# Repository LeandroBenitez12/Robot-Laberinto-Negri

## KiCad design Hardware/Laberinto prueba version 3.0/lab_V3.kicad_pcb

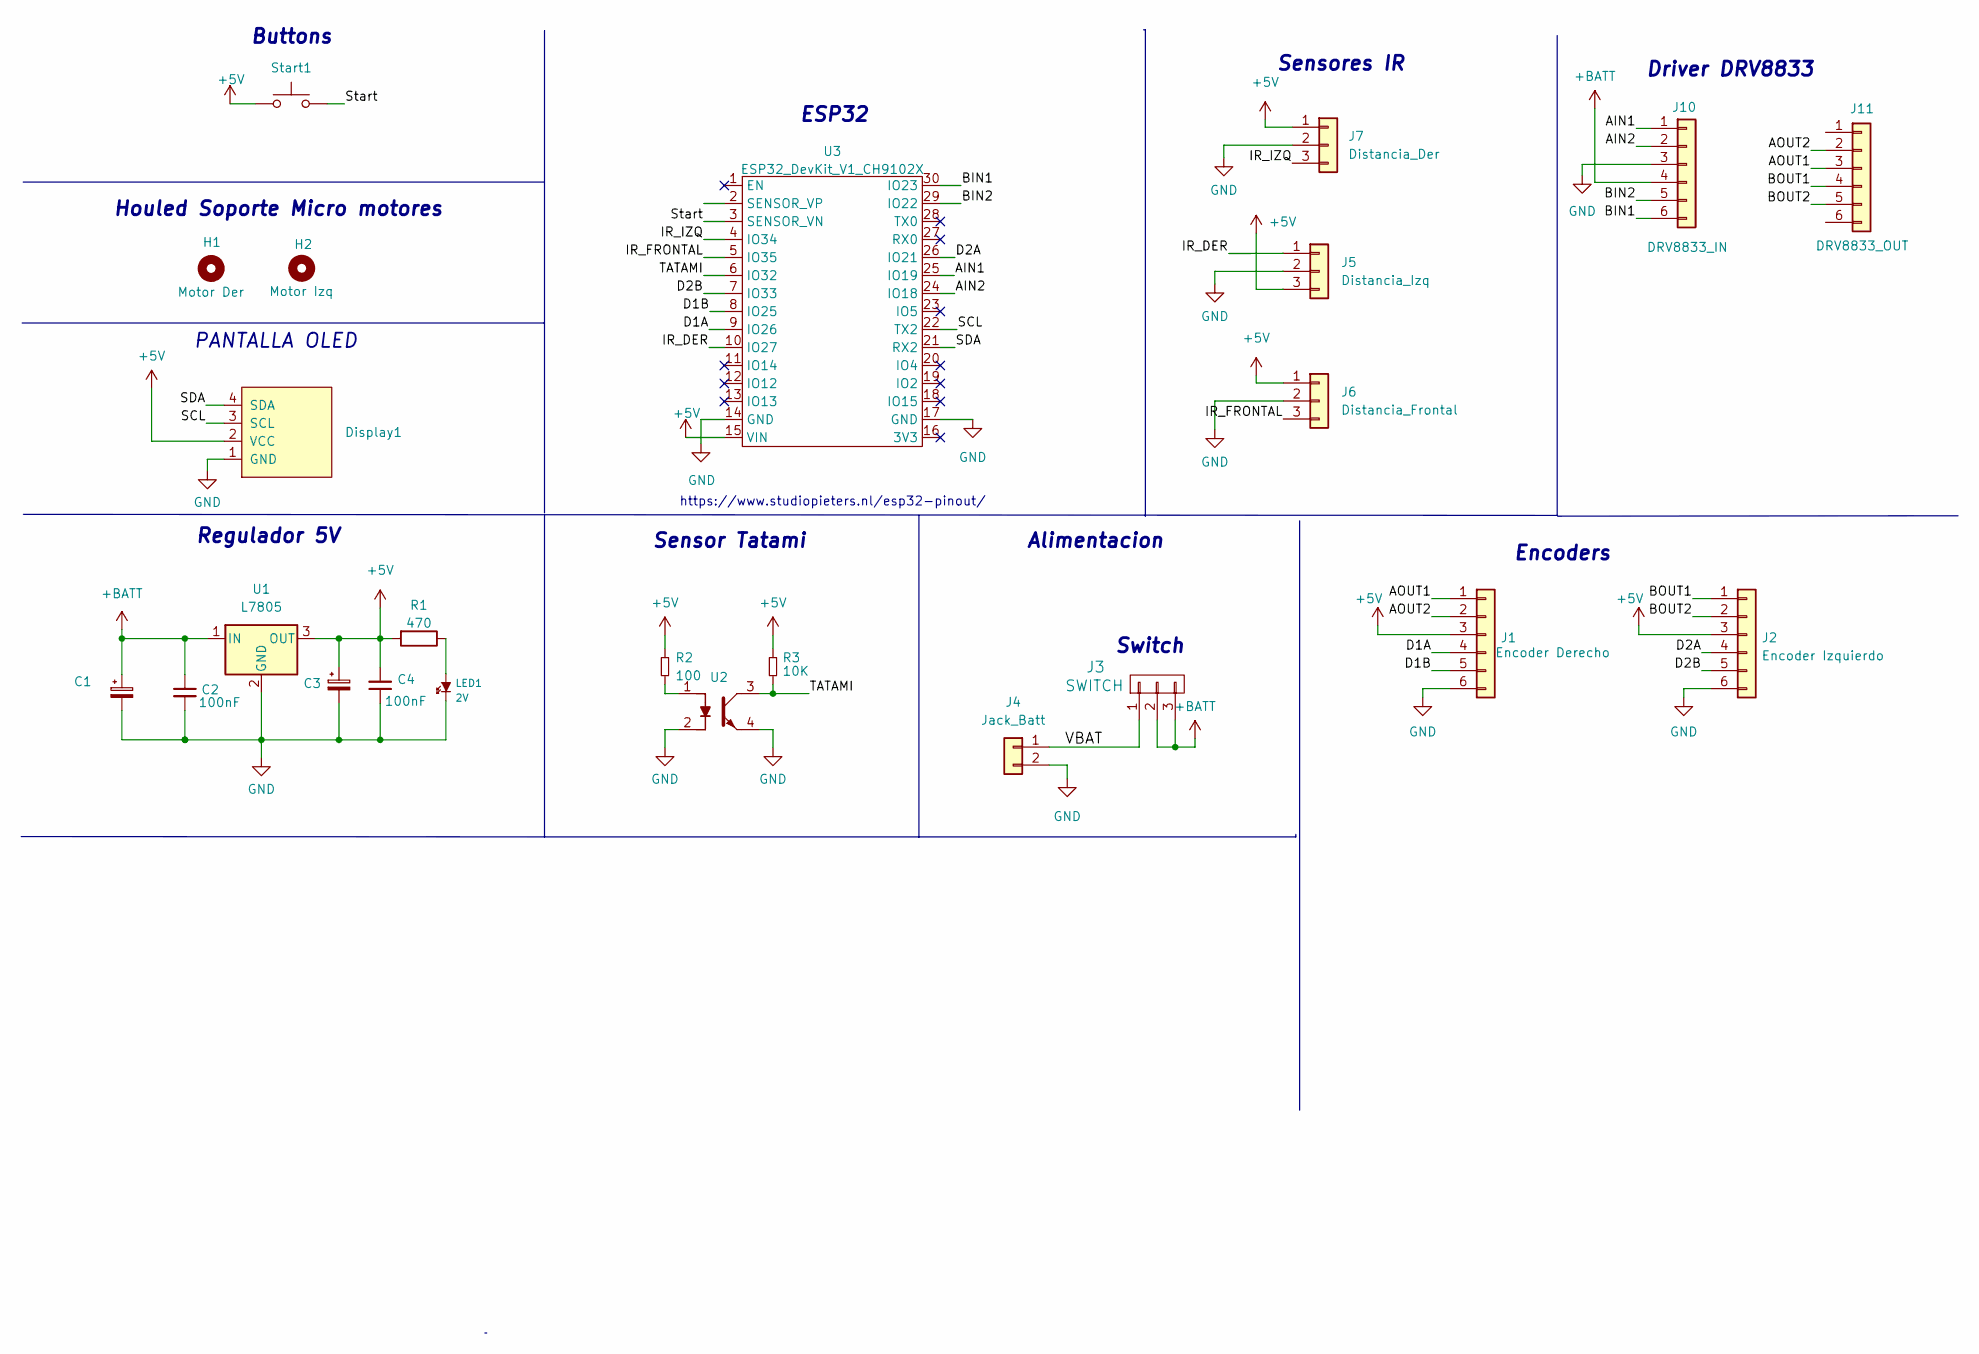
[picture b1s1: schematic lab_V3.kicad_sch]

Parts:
C1, C3: (no value)
C2, C4: 100nF; C_1206
Display1: SSD1306-SSD1306-128x64_OLED; 128x64OLED
H1: Motor Der; Pololu_Micro_Con_Soporte_Simple
H2: Motor Izq; Pololu_Micro_Con_Soporte_Simple
J1: Encoder Derecho; JST_EH_B6B-EH-A_1x06_P2.50mm_Vertical
J2: Encoder Izquierdo; JST_EH_B6B-EH-A_1x06_P2.50mm_Vertical
J3: SWITCH; SW_SPDT_TH_Vertical
J4: Jack_Batt; JST_EH_B2B-EH-A_1x02_P2.50mm_Vertical
J5: Distancia_Izq; JST_EH_B3B-EH-A_1x03_P2.50mm_Vertical
J6: Distancia_Frontal; JST_EH_B3B-EH-A_1x03_P2.50mm_Vertical
J7: Distancia_Der; JST_EH_B3B-EH-A_1x03_P2.50mm_Vertical
J10: DRV8833_IN; PinSocket_1x06_P2.54mm_Vertical
J11: DRV8833_OUT; PinSocket_1x06_P2.54mm_Vertical
LED1: 2V; led_5mm_green
R1: 470; R_1206
R2: 100; R_1206
R3: 10K; R_1206
Start1: SW_Push; Pulsador_TH_4
U1: L7805; SOT223
U2: QRE1113; QRE1113GR
U3: ESP32_DevKit_V1_CH9102X

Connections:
+5V: C3.1, C4.2, Display1.2 (VCC), J1.3, J2.3, J5.3, J6.1, J7.1, R1.2, R2.1, R3.1, Start1.1, U1.3 (OUT), U3.15 (VIN)
+BATT: C1.1, C2.1, J3.2, J3.3, J10.4, U1.1 (IN)
/AIN1: J10.1, U3.25 (IO19)
/AIN2: J10.2, U3.24 (IO18)
/AOUT1: J1.1, J11.3
/AOUT2: J1.2, J11.2
/BIN1: J10.6, U3.30 (IO23)
/BIN2: J10.5, U3.29 (IO22)
/BOUT1: J2.1, J11.4
/BOUT2: J2.2, J11.5
/D1A: J1.4, U3.9 (IO26)
/D1B: J1.5, U3.8 (IO25)
/D2A: J2.4, U3.26 (IO21)
/D2B: J2.5, U3.7 (IO33)
/IR_DER: J5.1, U3.10 (IO27)
/IR_FRONTAL: J6.3, U3.5 (IO35)
/IR_IZQ: J7.3, U3.4 (IO34)
/SCL: Display1.3 (SCL), U3.22 (TX2)
/SDA: Display1.4 (SDA), U3.21 (RX2)
/Start: Start1.2, U3.3 (SENSOR_VN)
/TATAMI: R3.2, U2.3, U3.6 (IO32)
/VBAT: J3.1, J4.1
GND: C1.2, C2.2, C3.2, C4.1, Display1.1 (GND), J1.6, J2.6, J4.2, J5.2, J6.2, J7.2, J10.3, LED1.2 (K), U1.2 (GND), U2.2, U2.4, U3.14 (GND), U3.17 (GND)
unnamed: LED1.1 (A), R1.1
unnamed: R2.2, U2.1

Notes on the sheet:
https://www.studiopieters.nl/esp32-pinout/
Sensor Tatami
Driver DRV8833
PANTALLA OLED
ESP32
Switch
Regulador 5V
Houled Soporte Micro motores
Encoders
Alimentacion
Buttons
Sensores IR

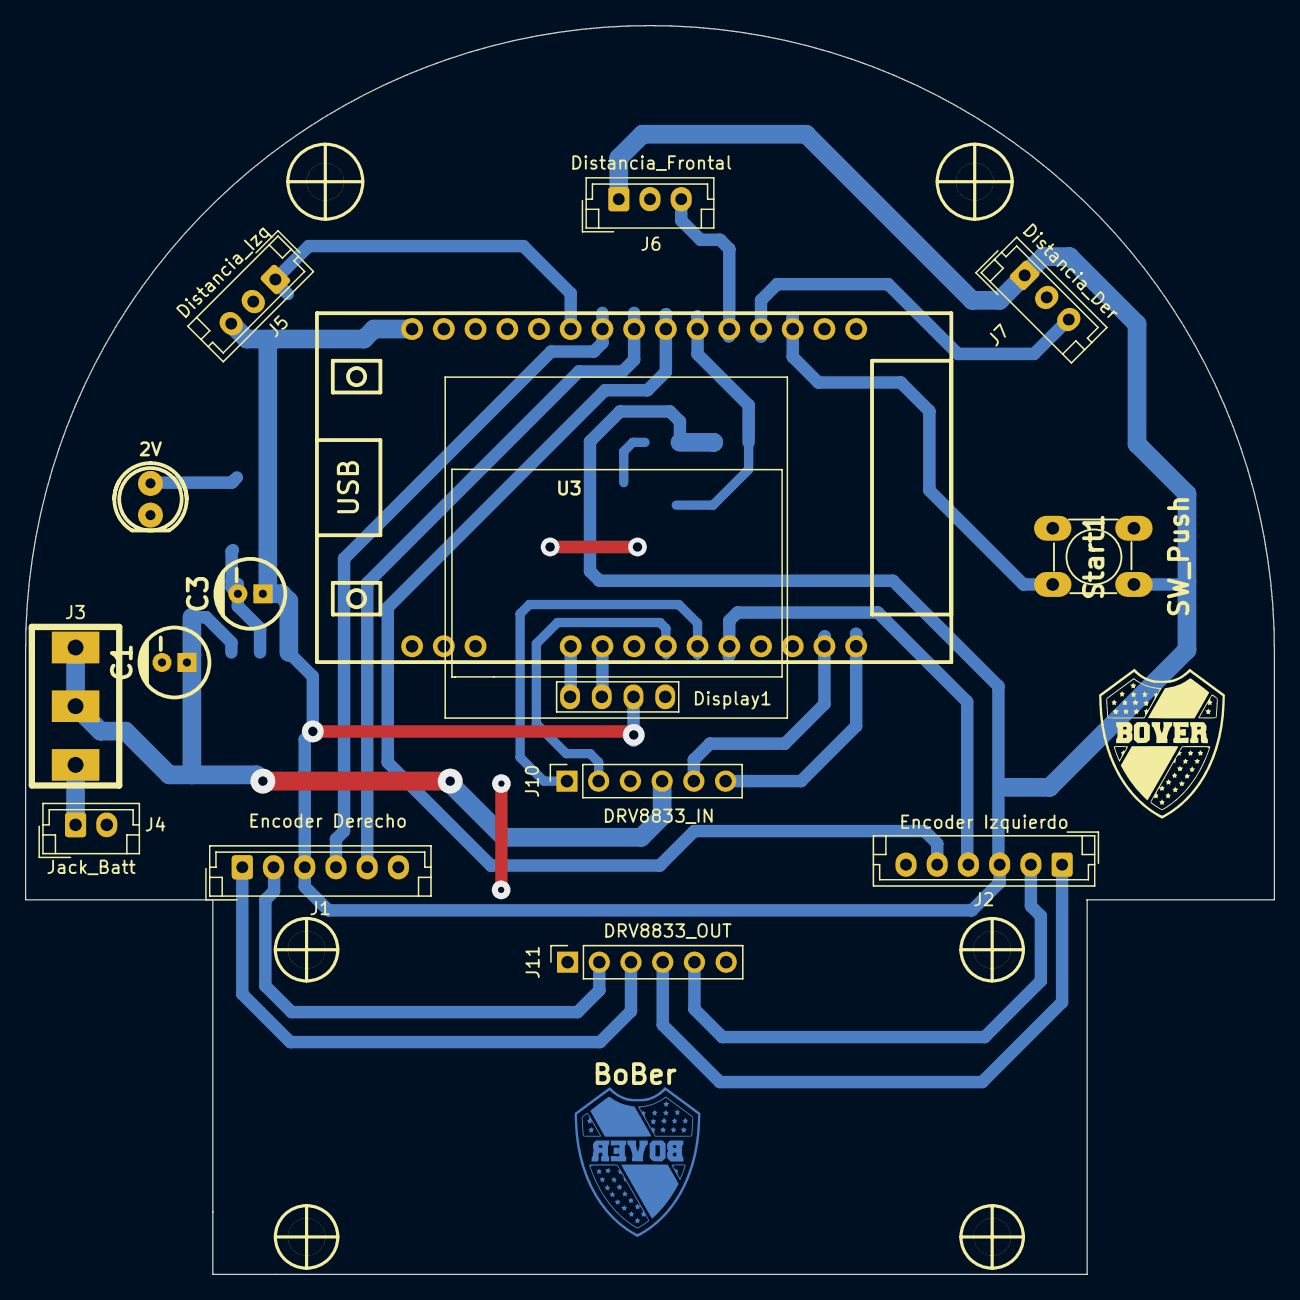
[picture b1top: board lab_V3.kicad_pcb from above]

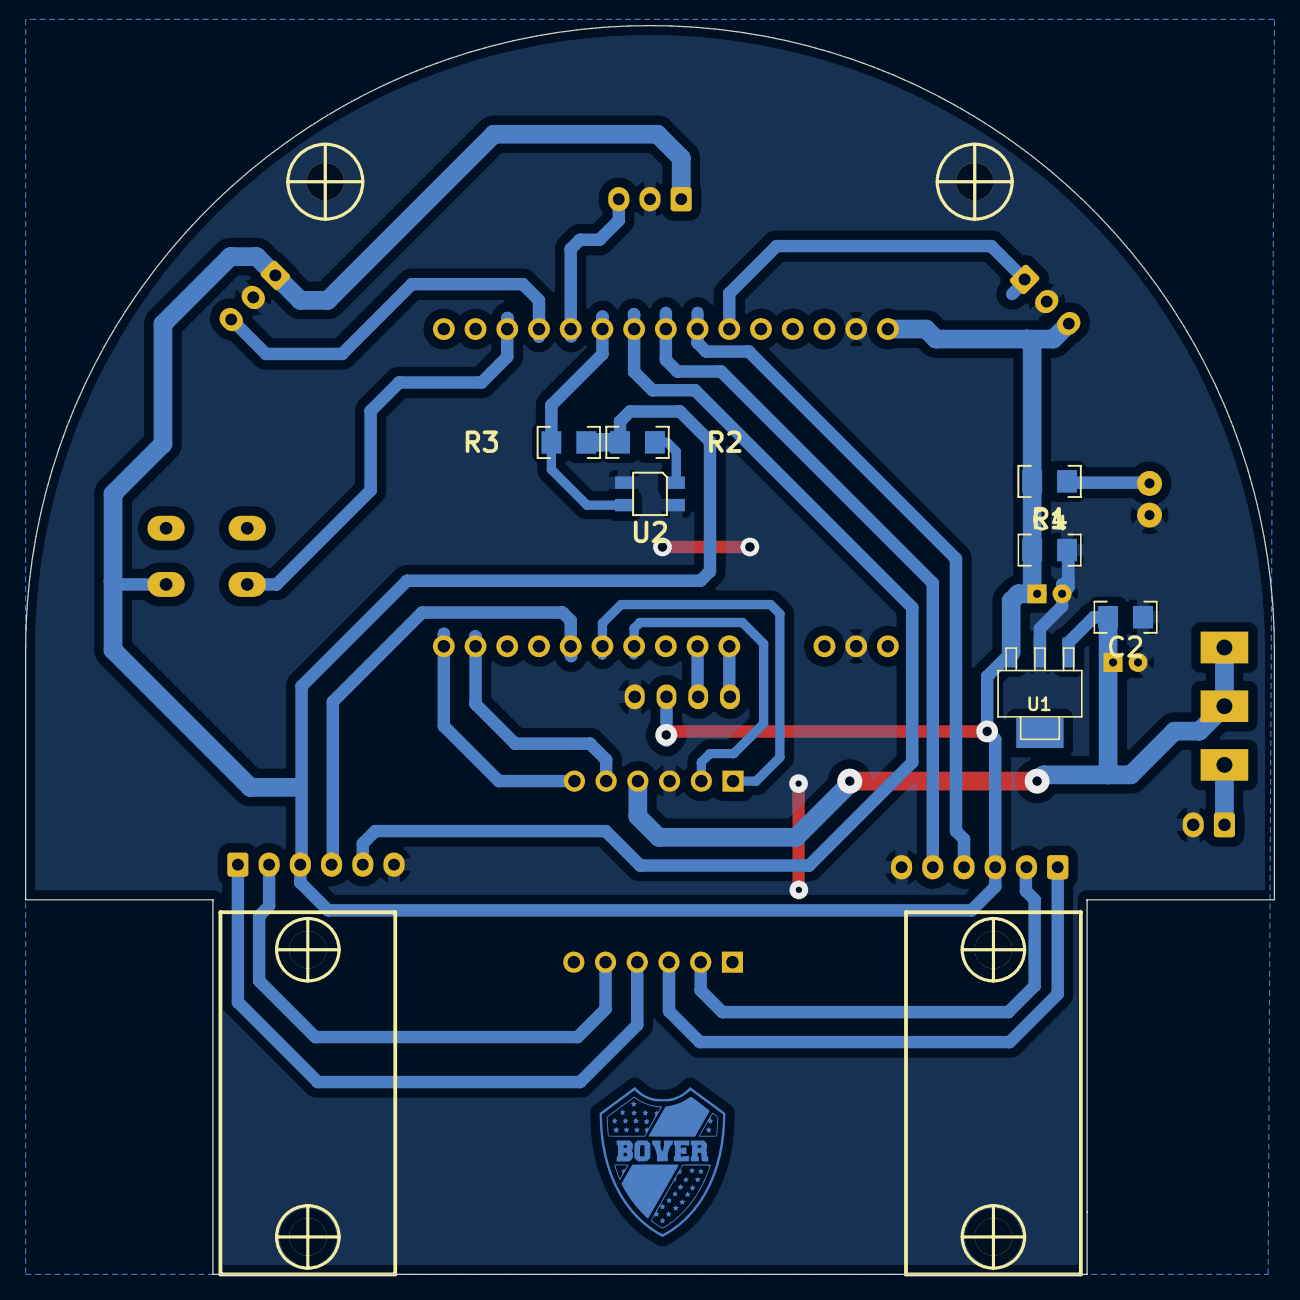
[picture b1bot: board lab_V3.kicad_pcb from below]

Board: 2 copper layers, 100.0 x 100.0 mm, 27 parts (9 on the bottom side), 25 nets.

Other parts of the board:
BoBer: LOGO; LOGO_BOVER_SER
hole_3mm, hole_3mm#2: VAL**; hole_3mm

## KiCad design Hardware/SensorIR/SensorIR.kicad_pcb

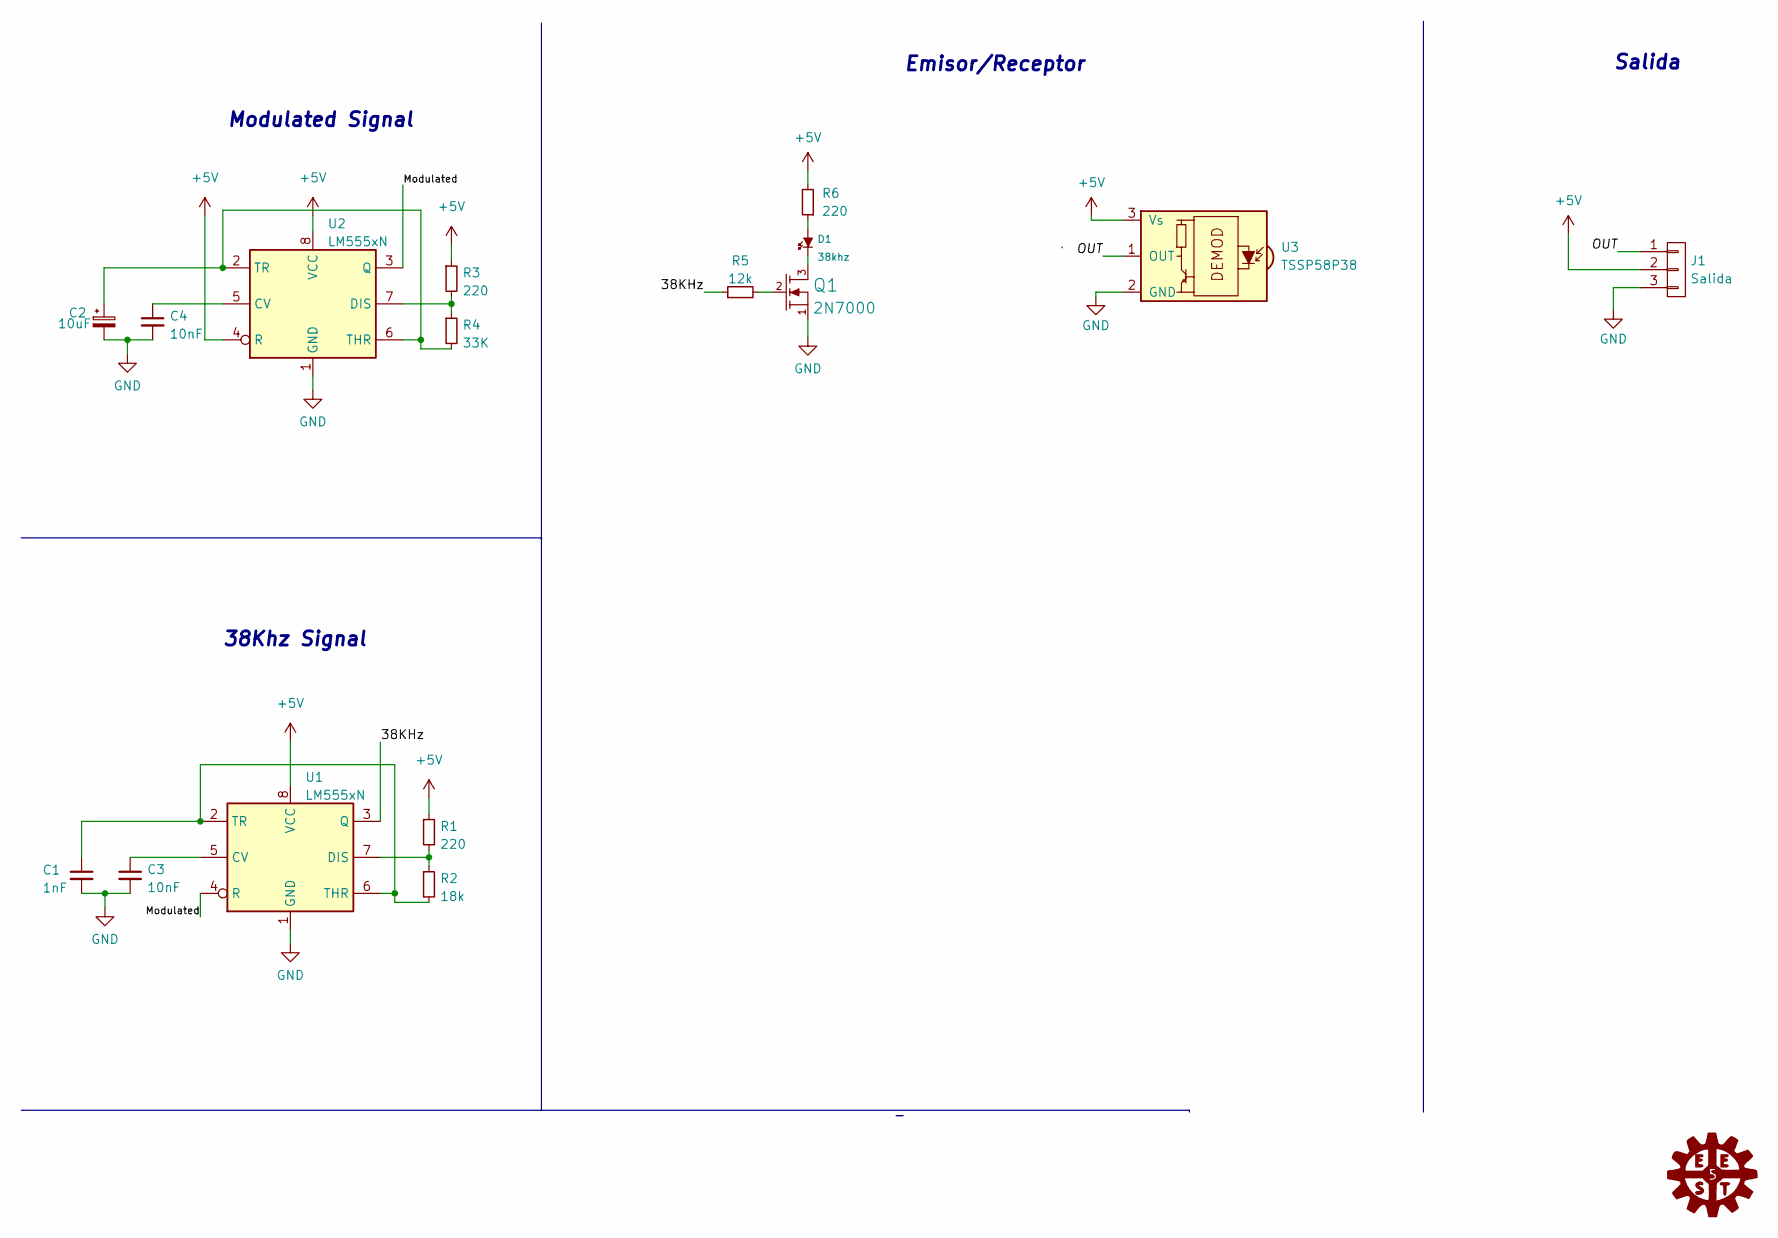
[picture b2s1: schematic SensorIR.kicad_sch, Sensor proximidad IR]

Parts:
C1: 1nF; C_1206
C2: 10uF; CAP_ELEC_5x11mm
C3, C4: 10nF; C_1206
D1: 38khz; led_5mm_clear
J1: Salida; Pin_Strip_3
Q1: 2N7000; to92
R1, R3, R6: 220; R_1206
R2: 18k; R_1206
R4: 33K; R_1206
R5: 12k; R_1206
U1, U2: LM555xN; SOIC-8_Hand_Soldering
U3: TSSP58P38; Vishay_MINICAST-3Pin

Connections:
+5V: J1.2, R1.1, R3.1, R6.2, U1.8 (VCC), U2.4 (R), U2.8 (VCC), U3.3 (Vs)
/38KHz: R5.1, U1.3 (Q)
/Modulated: U1.4 (R), U2.3 (Q)
/OUT: J1.1, U3.1 (OUT)
GND: C1.2, C2.2, C3.2, C4.2, J1.3, Q1.1 (S), U1.1 (GND), U2.1 (GND), U3.2 (GND)
unnamed: C1.1, R2.2, U1.2 (TR), U1.6 (THR)
unnamed: C2.1, R4.2, U2.2 (TR), U2.6 (THR)
unnamed: C3.1, U1.5 (CV)
unnamed: C4.1, U2.5 (CV)
unnamed: D1.1 (A), R6.1
unnamed: D1.2 (K), Q1.3 (D)
unnamed: Q1.2 (G), R5.2
unnamed: R1.2, R2.1, U1.7 (DIS)
unnamed: R3.2, R4.1, U2.7 (DIS)

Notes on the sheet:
Emisor/Receptor
38Khz Signal
Salida
Modulated Signal

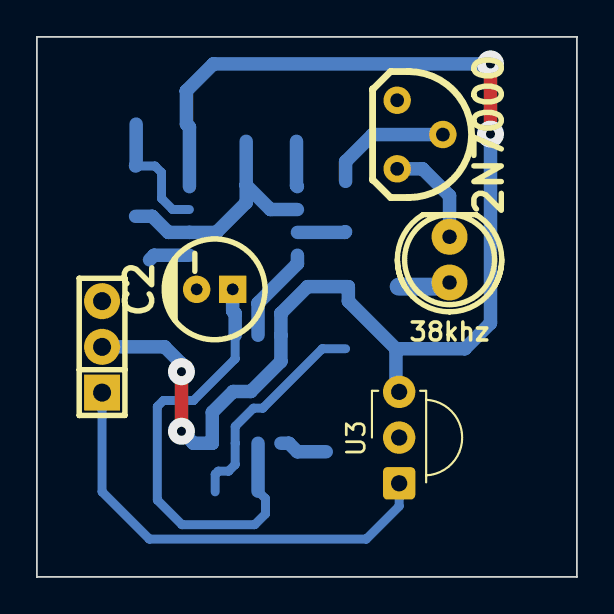
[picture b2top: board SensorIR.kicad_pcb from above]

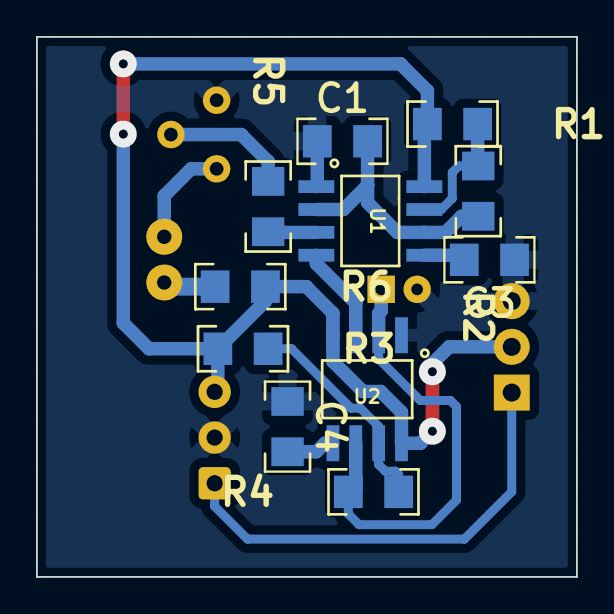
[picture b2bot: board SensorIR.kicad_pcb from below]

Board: 2 copper layers, 30.0 x 30.0 mm, 16 parts (11 on the bottom side), 14 nets.

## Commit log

2022-09-05 Add sch and design the IR Support
2022-09-17 PCB de taiel hay que continuar...
2022-09-18 SENSORES IR SCH
2022-09-18 continuamos PCB
2022-09-19 sch cambio
2022-09-19 sch cambio2
2022-09-20 Placa lista solo faltan alguna correcciones de taiel
2022-09-20 solucione conflictos de sch
2022-09-21 estamos haciendo la placa ya
2022-10-01 agrego Placa para eze
2022-10-12 ordenando
2022-10-15 subo el sch con el esp32 ya listo como para programar, faltan conexiones y definir el driver
2022-10-27 cambios en el diseño 3d de soportes IR
2022-10-28 add drivers de motores , falta ordenar pines, y borre IR de la primera version prueba de Bover lo voy a hacer externamente y estoy viendo la pisibilidad de agregar el uart usb directo a la placa
2022-10-30 emepzando con la conexiones uart/usb del esp32
